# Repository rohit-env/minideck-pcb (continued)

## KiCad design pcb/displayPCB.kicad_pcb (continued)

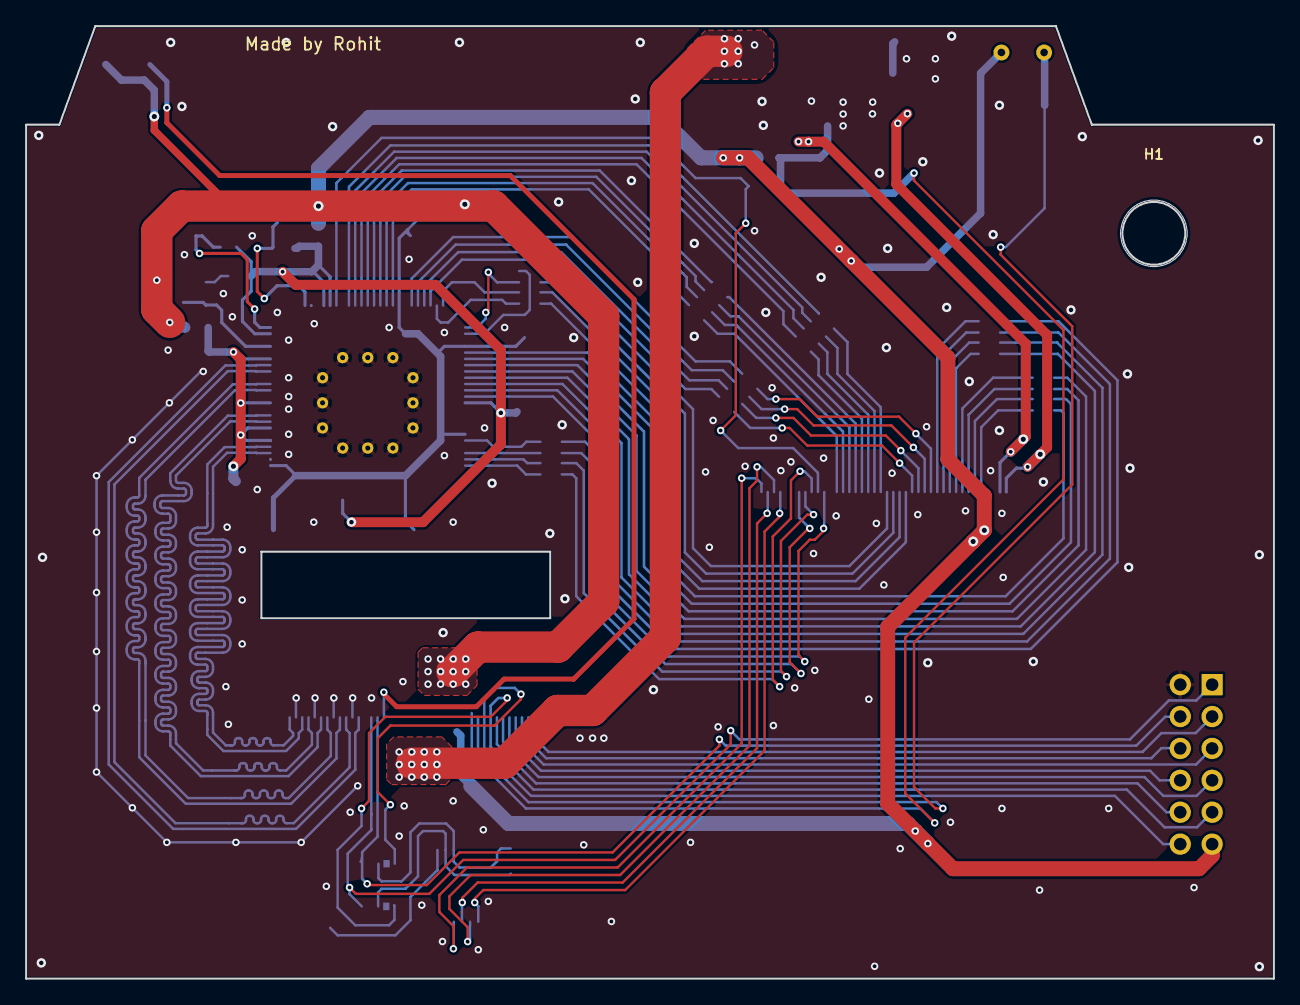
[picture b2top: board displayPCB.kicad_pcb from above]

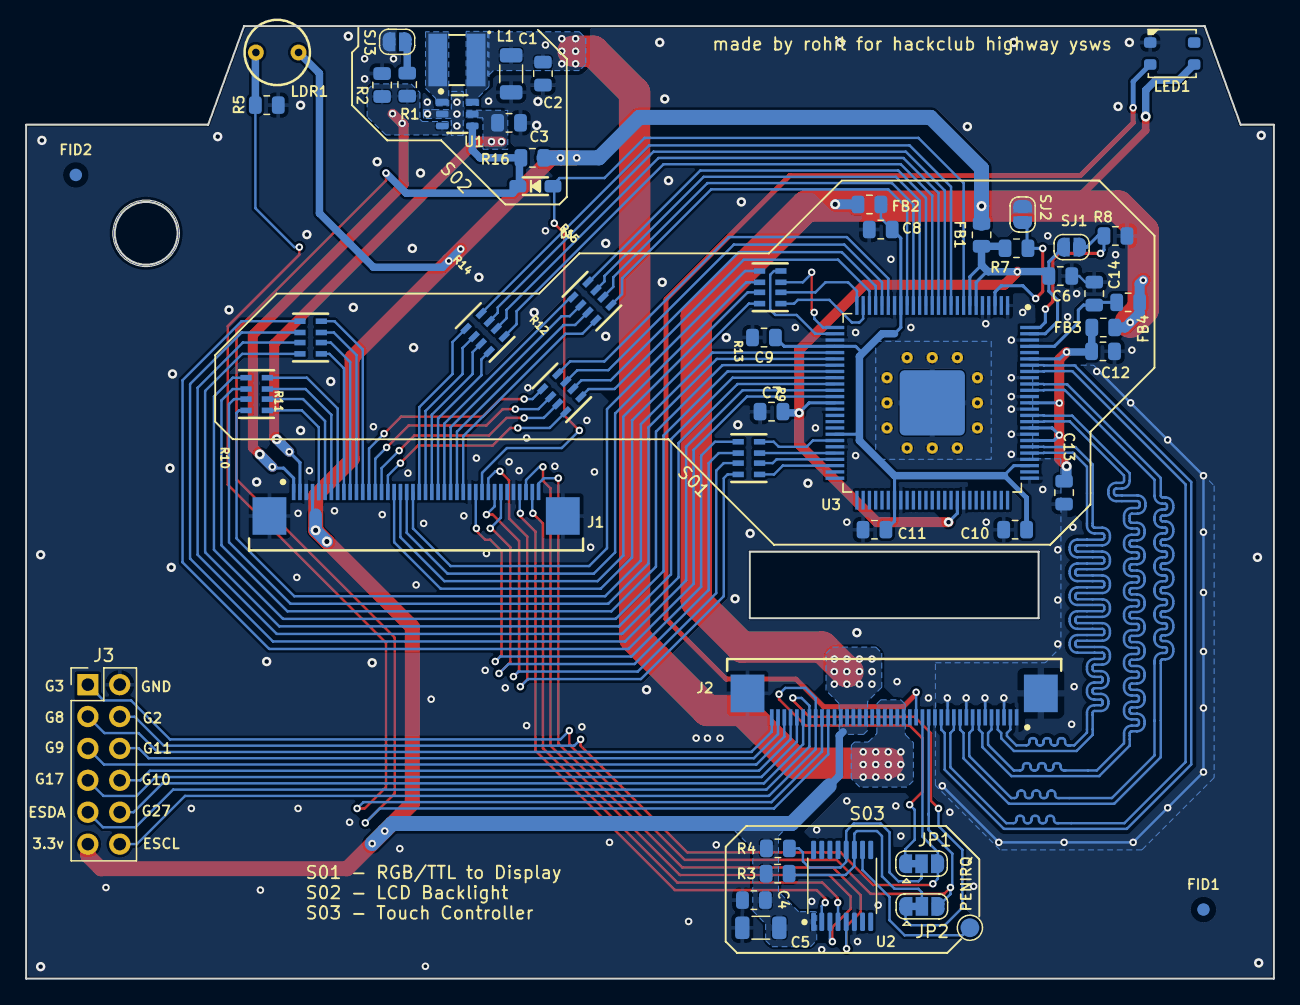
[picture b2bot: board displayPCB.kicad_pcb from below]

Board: 2 copper layers, 99.4 x 75.8 mm, 52 parts (51 on the bottom side), 98 nets.

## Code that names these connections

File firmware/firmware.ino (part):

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#define HA 8
#define VA 10
#define MOUSE_MID_BUTTON 9
#define LDR 14
#define LCD_BACKLIGHT 13
#define POWER_BUTTON 12
#define POWER_MAIN 11

// System feature
bool POWER_BUTTON_TO_POWER_OFF = true;
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}

void setup(void) {
  pinMode(POWER_MAIN, OUTPUT);
  digitalWrite(POWER_MAIN, HIGH);

  pinMode(LDR, INPUT);
  pinMode(VA, INPUT);
  pinMode(HA, INPUT);
  pinMode(MOUSE_MID_BUTTON, INPUT_PULLUP);
  pinMode(POWER_BUTTON, INPUT_PULLUP);
  pinMode(LCD_BACKLIGHT, OUTPUT);

  // Serial setup
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
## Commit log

2025-08-01 Add STEP and F3Z files with Git LFS
